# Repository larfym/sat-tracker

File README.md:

# 🛰️ Satellite Tracker

An ESP32-based automated dual-axis antenna tracking system for Low Earth
Orbit (LEO) satellites, featuring real-time orbital prediction,
closed-loop motor control, and a web-based telemetry interface.

------------------------------------------------------------------------

## 📡 Description

**Satellite Tracker** is an embedded platform designed to automatically
track Low Earth Orbit (LEO) satellites in real time using orbital
prediction algorithms.

The system is powered by an ESP32 microcontroller, which:

-   Computes satellite position using the SGP4 orbital propagation model
-   Synchronizes time and geographic location via GPS
-   Controls a motorized offset dish antenna in azimuth and elevation
-   Provides telemetry and configuration through an integrated web
    interface

The platform is modular, scalable, and suitable for experimentation,
amateur satellite tracking, and engineering research.

------------------------------------------------------------------------

## 🚀 Features

-   Real-time satellite tracking using SGP4 orbit prediction
-   Automatic next-pass prediction
-   GPS-based time and position synchronization
-   Integrated web interface for monitoring and configuration
-   JSON API for remote telemetry access
-   Configurable antenna mechanical offsets
-   Satellite visibility calculation (eclipse / daylight / visible)
-   Scalable and modular firmware architecture
-   Manual and automatic tracking modes
-   Dual-axis mount control (azimuth & elevation)
-   Position feedback using reed switches
-   Motor current monitoring for protection and diagnostics
-   PI-based closed-loop position control

------------------------------------------------------------------------

## 📁 Proyect Structure

    sat-tracker/Firmware
    │
    ├── src/                 # Source code
    ├── include/             # Headers y configurations
    ├── data/                # Web Page (SPIFFS / LittleFS)
    ├── lib/                 # Libs
    ├── platformio.ini       # PlatformIO config.

------------------------------------------------------------------------

## 🔧 Hardware Requirements

-   ESP32 DevKit V1
-   GPS Module
-   Custom Power Interface Board
-   Custom Main Control Board
-   Azimuth and Elevation actuators
-   36V / 5A power supply

------------------------------------------------------------------------

## 💻 Software Dependencies

-   SGP4 -- Satellite orbit prediction\
    https://github.com/Hopperpop/Sgp4-Library

-   ESPAsyncWebServer -- Asynchronous web server\
    https://github.com/me-no-dev/ESPAsyncWebServer

-   TinyGPS++ -- GPS NMEA parsing\
    https://github.com/mikalhart/TinyGPSPlus

-   ArduinoJson -- JSON serialization and parsing\
    https://arduinojson.org/

All dependencies are automatically managed via PlatformIO.

------------------------------------------------------------------------

## 🛠 Building and Installation

1.  Clone this repository:

git clone https://github.com/larfym/sat-tracker.git

2.  Install PlatformIO: https://platformio.org/

3.  Open the Firmware folder in VS Code with the PlatformIO extension.

4.  Build and upload:

platformio run --target uploadfs platformio run --target upload

------------------------------------------------------------------------

## 🌐 Web Interface

To access the web interface:

1.  Connect to the ESP32 WiFi Access Point (Default SSID: SatTracker)
2.  Open your browser and navigate to:

http://tracker.local

From the web interface you can:

-   Configure satellite TLE data
-   Adjust antenna offsets
-   Monitor real-time telemetry
-   Switch between manual and automatic tracking
-   View GPS and system status
-   Monitor next pass prediction

## 📜 License

This project is licensed under the GNU General Public License v3.0 - see [LICENSE](LICENSE) for details.

------------------------------------------------------------------------

🛰 Satellite Tracker -- Embedded autonomous satellite tracking platform.

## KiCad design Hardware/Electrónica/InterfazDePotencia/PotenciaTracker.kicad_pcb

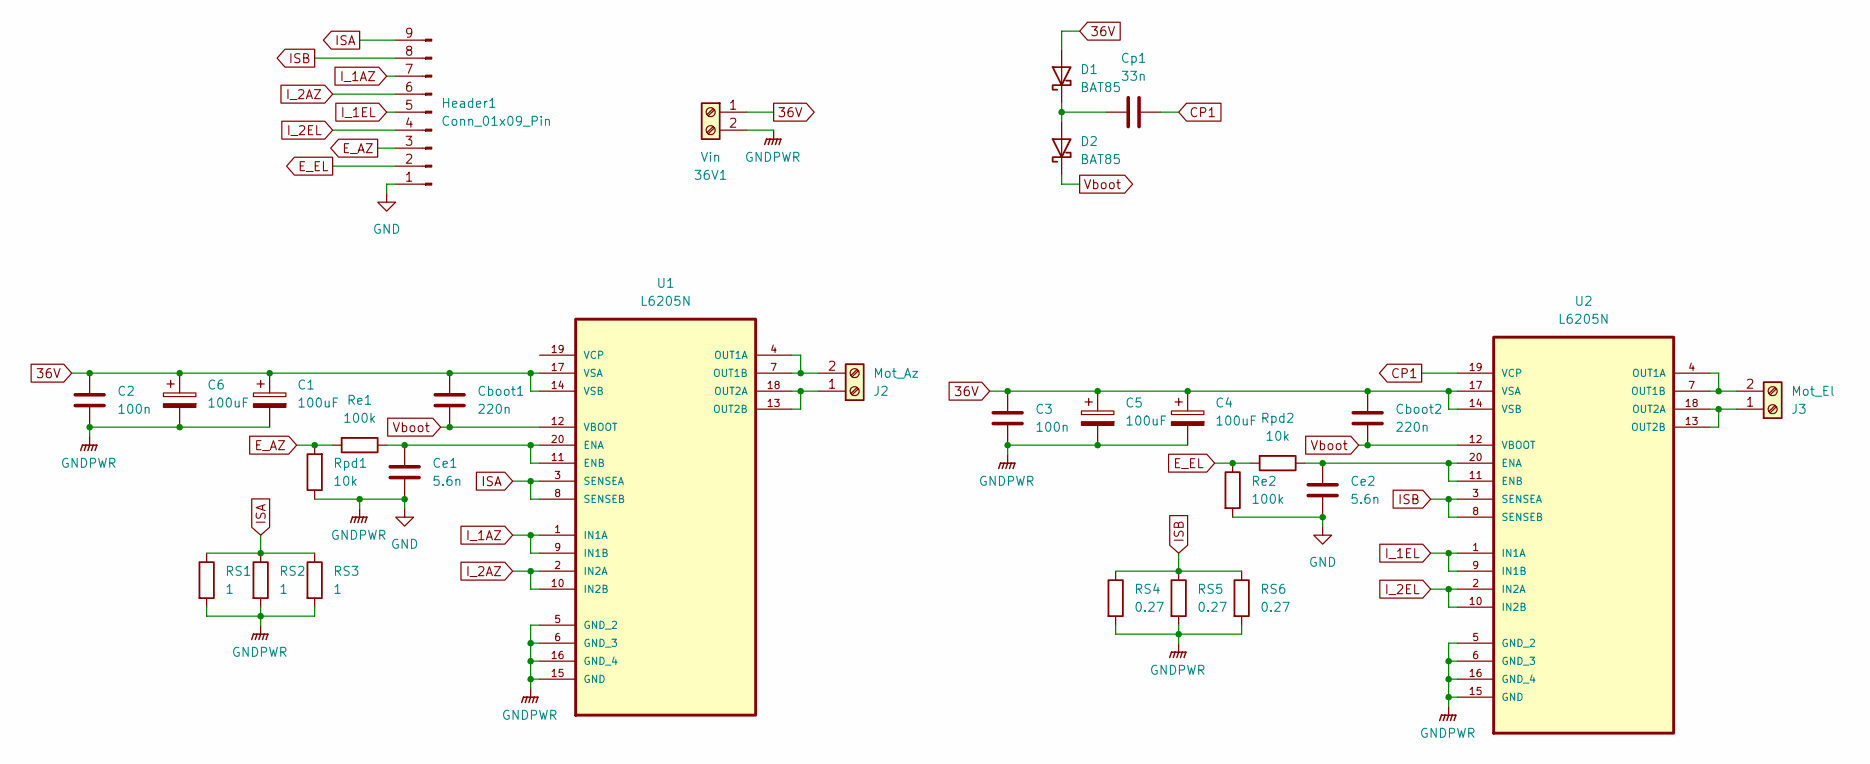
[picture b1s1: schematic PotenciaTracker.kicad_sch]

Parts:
36V1: Vin; TerminalBlock_MetzConnect_Type055_RT01502HDWU_1x02_P5.00mm_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
C1, C4, C5, C6: 100uF; CP_Radial_D8.0mm_P3.50mm
C2, C3: 100n; C_Axial_L3.8mm_D2.6mm_P7.50mm_Horizontal
Cboot1, Cboot2: 220n; C_Axial_L3.8mm_D2.6mm_P7.50mm_Horizontal
Ce1, Ce2: 5.6n; C_Disc_D5.0mm_W2.5mm_P5.00mm
Cp1: 33n; C_Axial_L3.8mm_D2.6mm_P7.50mm_Horizontal
D1, D2: BAT85; D_DO-35_SOD27_P7.62mm_Horizontal
Header1: Conn_01x09_Pin; JST_XH_B9B-XH-A_1x09_P2.50mm_Vertical
J2: Mot_Az; TerminalBlock_MetzConnect_Type055_RT01502HDWU_1x02_P5.00mm_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
J3: Mot_El; TerminalBlock_MetzConnect_Type055_RT01502HDWU_1x02_P5.00mm_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
RS1, RS2, RS3: 1; R_Axial_DIN0207_L6.3mm_D2.5mm_P7.62mm_Horizontal
RS4, RS5, RS6: 0.27; R_Axial_DIN0411_L9.9mm_D3.6mm_P15.24mm_Horizontal
Re1, Re2: 100k; R_Axial_DIN0207_L6.3mm_D2.5mm_P7.62mm_Horizontal
Rpd1, Rpd2: 10k; R_Axial_DIN0207_L6.3mm_D2.5mm_P7.62mm_Horizontal
U1, U2: L6205N; CERDIP-20_W7.62mm_SideBrazed; MPN L6205N

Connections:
36V: 36V1.1, C1.1, C2.1, C3.1, C4.1, C5.1, C6.1, Cboot1.1, Cboot2.1, D1.2 (A), U1.14 (VSB), U1.17 (VSA), U2.14 (VSB), U2.17 (VSA)
CP1: Cp1.1, U2.19 (VCP)
E_AZ: Header1.3, Re1.2, Rpd1.2
E_EL: Header1.2, Re2.1, Rpd2.2
GND: 36V1.2, C1.2, C2.2, C3.2, C4.2, C5.2, C6.2, Ce1.2, Ce2.2, Header1.1, RS1.2, RS2.2, RS3.2, RS4.2, RS5.2, RS6.2, Re2.2, Rpd1.1, U1.5 (GND_2), U1.6 (GND_3), U1.15 (GND), U1.16 (GND_4), U2.5 (GND_2), U2.6 (GND_3), U2.15 (GND), U2.16 (GND_4)
ISA: Header1.9, RS1.1, RS2.1, RS3.1, U1.3 (SENSEA), U1.8 (SENSEB)
ISB: Header1.8, RS4.1, RS5.1, RS6.1, U2.3 (SENSEA), U2.8 (SENSEB)
I_1AZ: Header1.7, U1.1 (IN1A), U1.9 (IN1B)
I_1EL: Header1.5, U2.1 (IN1A), U2.9 (IN1B)
I_2AZ: Header1.6, U1.2 (IN2A), U1.10 (IN2B)
I_2EL: Header1.4, U2.2 (IN2A), U2.10 (IN2B)
unnamed: Cp1.2, D1.1 (K), D2.2 (A)
unnamed: J2.1, U1.13 (OUT2B), U1.18 (OUT2A)
unnamed: J2.2, U1.4 (OUT1A), U1.7 (OUT1B)
unnamed: J3.1, U2.13 (OUT2B), U2.18 (OUT2A)
unnamed: J3.2, U2.4 (OUT1A), U2.7 (OUT1B)
unnamed: Ce1.1, Re1.1, U1.11 (ENB), U1.20 (ENA)
unnamed: Ce2.1, Rpd2.1, U2.11 (ENB), U2.20 (ENA)
Vboot: Cboot1.2, Cboot2.2, D2.1 (K), U1.12 (VBOOT), U2.12 (VBOOT)

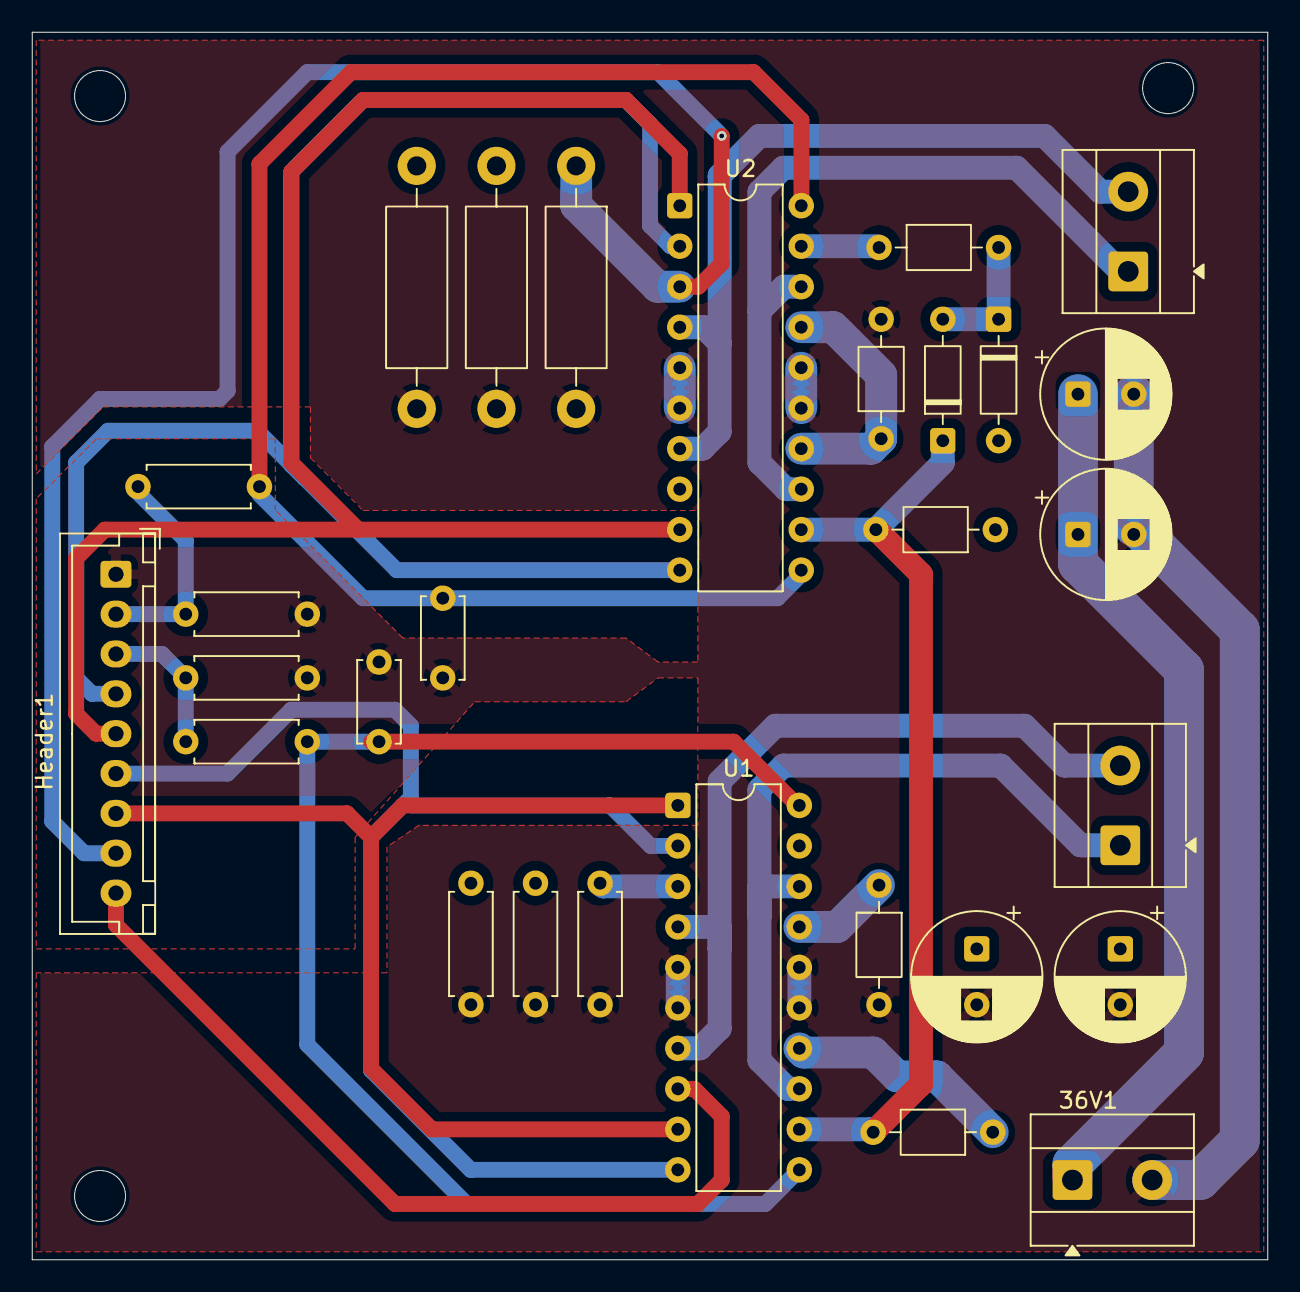
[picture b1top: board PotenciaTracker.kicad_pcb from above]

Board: 2 copper layers, 77.5 x 77.0 mm, 29 parts (0 on the bottom side), 19 nets.

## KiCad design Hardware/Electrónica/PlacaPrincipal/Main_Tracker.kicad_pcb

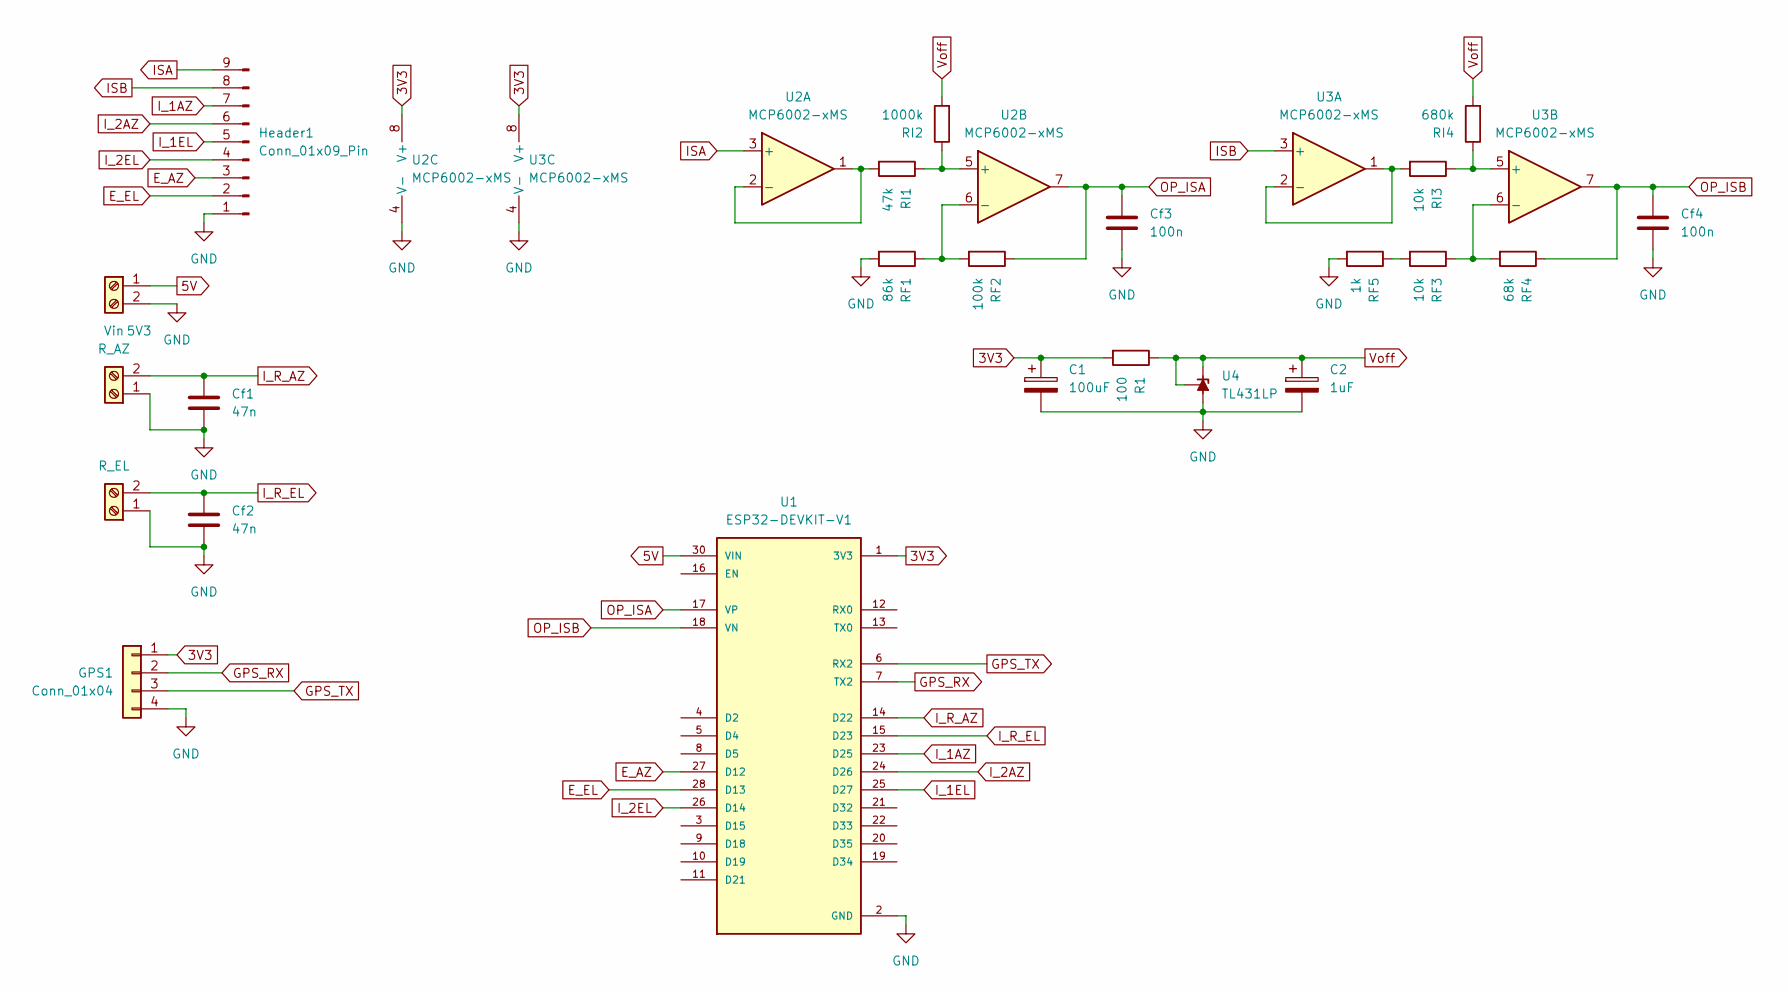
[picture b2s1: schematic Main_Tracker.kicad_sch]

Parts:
5V1: R_AZ; TerminalBlock_MetzConnect_Type055_RT01502HDWU_1x02_P5.00mm_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
5V2: R_EL; TerminalBlock_MetzConnect_Type055_RT01502HDWU_1x02_P5.00mm_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
5V3: Vin; TerminalBlock_MetzConnect_Type055_RT01502HDWU_1x02_P5.00mm_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
C1: 100uF; CP_Radial_D6.3mm_P2.50mm
C2: 1uF; CP_Radial_D6.3mm_P2.50mm
Cf1, Cf2: 47n; C_Disc_D5.0mm_W2.5mm_P5.00mm
Cf3, Cf4: 100n; C_Disc_D5.0mm_W2.5mm_P5.00mm
GPS1: Conn_01x04; PinHeader_1x04_P2.00mm_Vertical
Header1: Conn_01x09_Pin; JST_XH_B9B-XH-A_1x09_P2.50mm_Vertical
R1: 100; R_Axial_DIN0207_L6.3mm_D2.5mm_P7.62mm_Horizontal
RF1: 86k; R_Axial_DIN0207_L6.3mm_D2.5mm_P7.62mm_Horizontal
RF2: 100k; R_Axial_DIN0207_L6.3mm_D2.5mm_P7.62mm_Horizontal
RF3: 10k; R_Axial_DIN0207_L6.3mm_D2.5mm_P7.62mm_Horizontal
RF4: 68k; R_Axial_DIN0207_L6.3mm_D2.5mm_P7.62mm_Horizontal
RF5: 1k; R_Axial_DIN0207_L6.3mm_D2.5mm_P7.62mm_Horizontal
RI1: 47k; R_Axial_DIN0207_L6.3mm_D2.5mm_P7.62mm_Horizontal
RI2: 1000k; R_Axial_DIN0207_L6.3mm_D2.5mm_P7.62mm_Horizontal
RI3: 10k; R_Axial_DIN0207_L6.3mm_D2.5mm_P7.62mm_Horizontal
RI4: 680k; R_Axial_DIN0207_L6.3mm_D2.5mm_P7.62mm_Horizontal
U1: ESP32-DEVKIT-V1; MODULE_ESP32_DEVKIT_V1; PARTREV N/A
U2, U3: MCP6002-xMS; DIP-8_W7.62mm_LongPads
U4: TL431LP; TO-92_Inline_Wide

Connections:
3V3: C1.1, GPS1.1, R1.2, U1.1 (3V3), U2.8 (V+), U3.8 (V+)
5V: 5V3.1, U1.30 (VIN)
E_AZ: Header1.3, U1.27 (D12)
E_EL: Header1.2, U1.28 (D13)
GND: 5V1.1, 5V2.1, 5V3.2, C1.2, C2.2, Cf1.2, Cf2.2, Cf3.2, Cf4.2, GPS1.4, Header1.1, RF1.2, RF5.2, U1.2 (GND), U1.29 (GND), U2.4 (V-), U3.4 (V-), U4.2 (A)
GPS_RX: GPS1.2, U1.7 (TX2)
GPS_TX: GPS1.3, U1.6 (RX2)
ISA: Header1.9, U2.3 (+)
ISB: Header1.8, U3.3 (+)
I_1AZ: Header1.7, U1.23 (D25)
I_1EL: Header1.5, U1.25 (D27)
I_2AZ: Header1.6, U1.24 (D26)
I_2EL: Header1.4, U1.26 (D14)
I_R_AZ: 5V1.2, Cf1.1, U1.14 (D22)
I_R_EL: 5V2.2, Cf2.1, U1.15 (D23)
unnamed: RF3.2, RF5.1
unnamed: RI1.2, U2.1, U2.2 (-)
unnamed: RI1.1, RI2.1, U2.5 (+)
unnamed: RF1.1, RF2.2, U2.6 (-)
unnamed: RI3.2, U3.1, U3.2 (-)
unnamed: RI3.1, RI4.1, U3.5 (+)
unnamed: RF3.1, RF4.2, U3.6 (-)
OP_ISA: Cf3.1, RF2.1, U1.17 (VP), U2.7
OP_ISB: Cf4.1, RF4.1, U1.18 (VN), U3.7
Voff: C2.1, R1.1, RI2.2, RI4.2, U4.1 (REF), U4.3 (K)

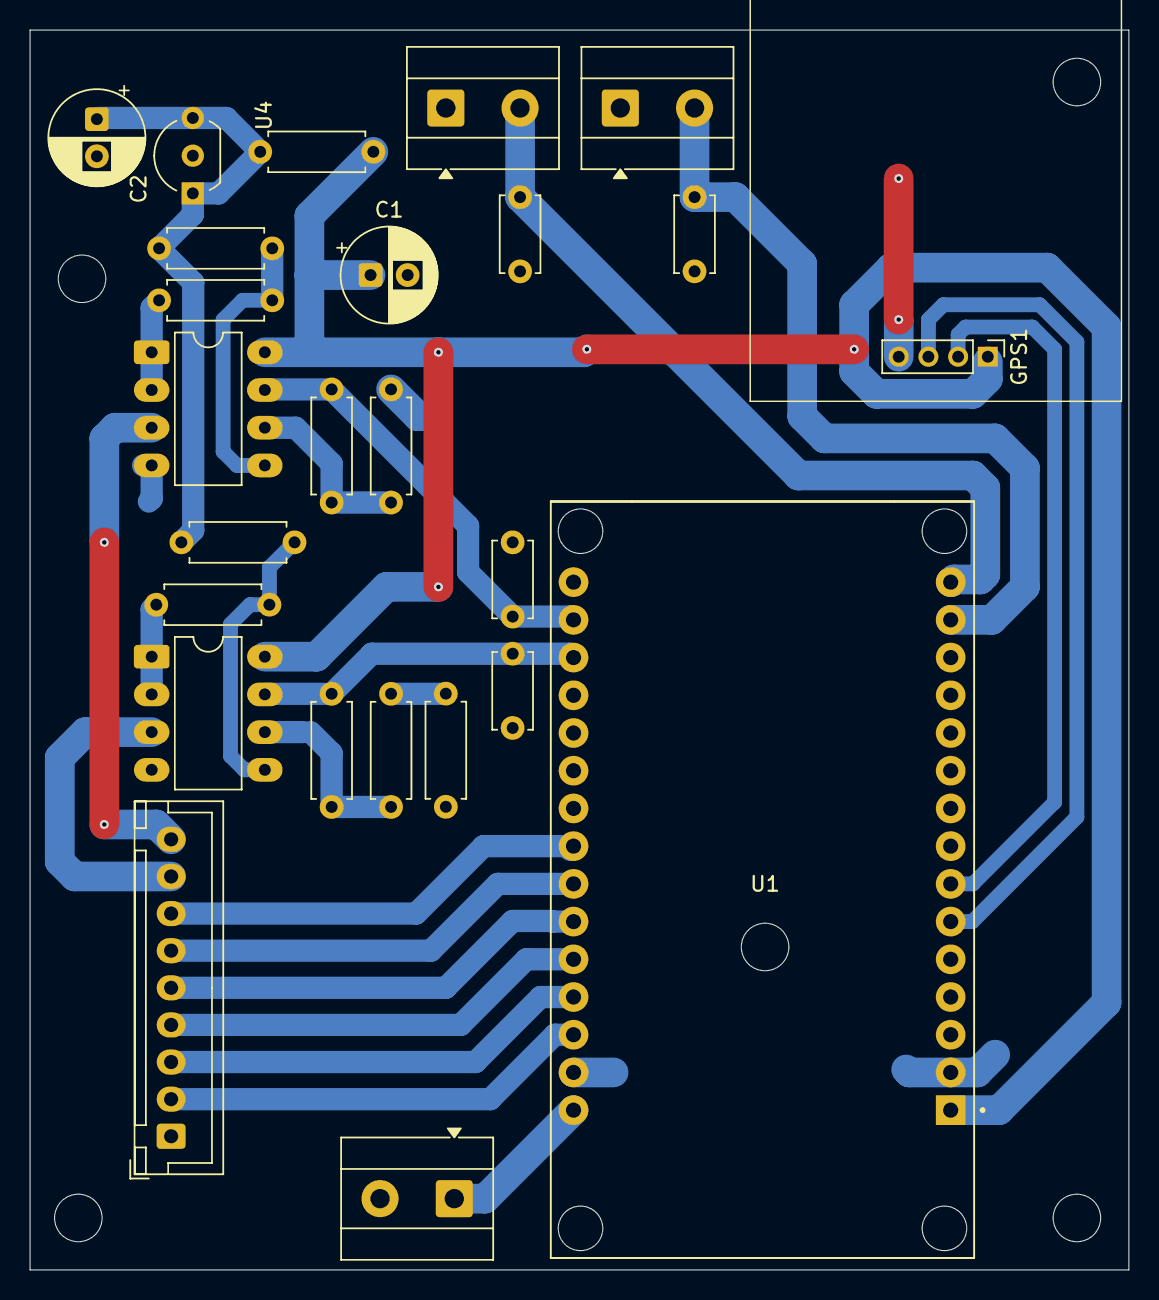
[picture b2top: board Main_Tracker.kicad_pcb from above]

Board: 2 copper layers, 74.0 x 83.5 mm, 25 parts (0 on the bottom side), 25 nets.

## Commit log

2025-10-31 HTTP Server Done, mDNS Done, Drivers Done.
2025-10-31 Current firmware
2025-11-14 new file: include/configurations.h Pin & Configs new file: include/currentSensor.h Added Offset calib modified: include/motorDriver.h Added NonLinelity
2025-11-14 File formatting
2025-11-16 modified: include/configurations.h General configurations modified: src/main.cpp Interpolation & RTC internal added modified: src/pid.cpp Functional changes modified: src/server.cpp structure improve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
2025-11-16 modified: include/utils.h Added LUT for faster calculations modified: src/utils.cpp Elevation non Linearity function implemented
2025-11-17 modified: data/index.html Moddified IU
2025-11-21 modified: include/configurations.h Added more Control definitions modified: include/utils.h Added non linearity functions modified: src/main.cpp Implemented Control/Movement algorithm modified: src/u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
2025-12-08 new file: include/PI_Controller.h Added discrete PI Controller modified: include/configurations.h PWM freq & Signal Adaptation changes
2025-12-10 minor changes
2025-12-15 Fixed minor bugs
2026-02-07 modified: data/index.html Added Graphs and styling modified: include/PI_Controller.h Low Pass on Input modified: include/configurations.h Added Frequency of Reed Switches modified: src/PI_Controller.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
2026-02-11 modified: src/main.cpp fix minor bug in main loop
2026-02-12 modified: include/PI_Controller.h Added reset modified: src/PI_Controller.cpp Added reset modified: src/main.cpp New efficient Control
2026-02-12 modified: include/configurations.h updated coeff
2026-02-17 modified: include/configurations.h constants and configurations
2026-02-17 Refactor: move firmware files to a dedicated 'Firmware' directory
2026-02-18 Archivos, piezas, documentación...
2026-02-18 modified: Firmware/data/index.html Added visibility modified: Firmware/src/main.cpp Added prediction of horizon crossing new file: "Hardware/Funci\303\263nTransferencia.xlsx"
2026-02-18 Revise README for clarity and additional details
    Updated README with enhanced descriptions, features, and project structure.
2026-02-18 Revise README for clarity and updated features
    Updated project description and features for clarity. Removed outdated sections and improved formatting.
2026-02-23 modified: Firmware/src/PI_Controller.cpp changed Tustin to Euler method
2026-02-25 modified: Firmware/data/index.html Fixed Graph bugs new file: Hardware/Dimensiones.png Mount Parameter Dimensions
2026-03-04 modified: Firmware/data/index.html change Telemetry w/SSE modified: Firmware/include/server.h change Telemetry w/SSE modified: Firmware/src/main.cpp Added next pass prediction fnc modified: Firmware/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
2026-03-04 modified: Firmware/src/main.cpp bg
2026-03-06 modified: Firmware/src/main.cpp Deleted reed filter & Smoother Control
2026-03-07 Added Doxy Doc & Minified HTML
2026-03-09 modified: Firmware/Docs/html/_formulas.log doc
2026-03-09 new file: Docs/Manual De Usuario.docx
2026-03-09 modified: Firmware/src/main.cpp Check Actual motor stop modified: Web_Interface/index.html Add auto-reconnect
2026-03-25 modified: Firmware/include/currentSensor.h modified: Firmware/include/server.h modified: Firmware/src/currentSensor.cpp modified: Firmware/src/main.cpp
2026-03-25 modified: Firmware/src/main.cpp
2026-04-06 modified: Firmware/data/index.html
2026-04-23 Agregrado documentación Tesis
